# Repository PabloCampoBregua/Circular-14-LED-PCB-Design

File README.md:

# Circular LED PCB

Design and development of a four-layer circular PCB featuring a 14-LED array for illumination purposes, designed using **KiCad 9.0**.

## Project Overview

This project focuses on the design of a compact circular printed circuit board (PCB) with 14 LEDs arranged in two concentric rings.

The PCB uses a four-layer architecture to simplify power distribution and ground connections while keeping the individual LED circuits properly routed.

## Technical Specifications

- **EDA software:** KiCad 9.0
- **PCB type:** Four-layer PCB
- **LED configuration:** 14 LEDs arranged in two concentric rings
- **LED drivers:** Individual series resistor for each LED
- **Power distribution:** Dedicated internal copper layer
- **Ground distribution:** Dedicated internal copper layer

## PCB Layer Stack-up

| Layer | Function |
|---|---|
| F.Cu | LED components and signal routing |
| In1.Cu | Ground plane (GND) |
| In2.Cu | Power distribution plane (+V) |
| B.Cu | Current-limiting resistors and routing |

## Design Features

- Circular PCB geometry.
- Two concentric LED arrays.
- Individual current-limiting resistors for each LED.
- Dedicated internal copper planes for power and ground distribution.
- Through-hole vias connecting surface components to internal copper layers.

## Repository Structure

- `.kicad_pro` – KiCad project configuration.
- `.kicad_pcb` – PCB layout.
- `.kicad_sch` – Electrical schematic, if available.
- `README.md` – Project documentation.

## PCB Design

### 3D View

### Front View

### Back View

## Tools

- KiCad 9.0

## Project Status

PCB layout and routing completed. Final design validation pending.

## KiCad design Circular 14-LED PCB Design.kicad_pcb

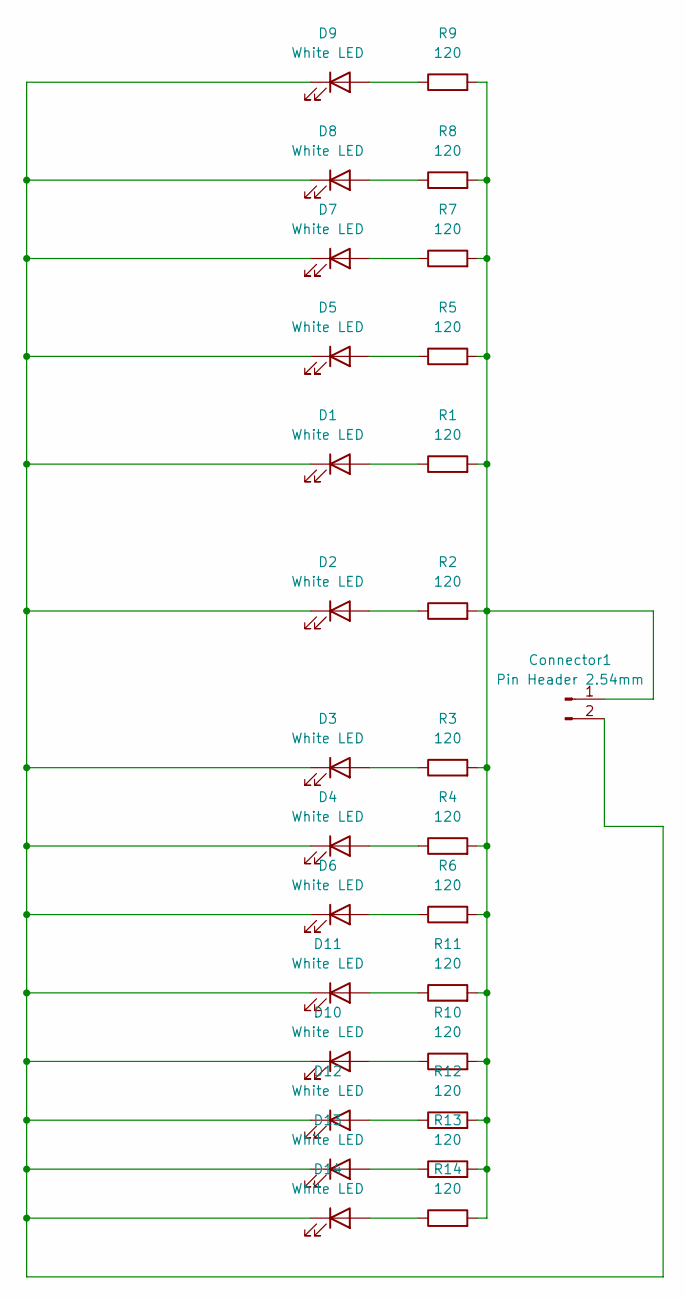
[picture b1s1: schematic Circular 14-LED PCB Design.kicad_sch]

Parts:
Connector1: Pin Header 2.54mm; PinHeader_1x02_P2.54mm_Vertical
D1, D2, D3, D4, D5, D6, D7, D8, D9, D10, D11, D12, D13, D14: White LED; LED_1206_3216Metric_Pad1.42x1.75mm_HandSolder
R1, R2, R3, R4, R5, R6, R7, R8, R9, R10, R11, R12, R13, R14: 120; R_1206_3216Metric_Pad1.30x1.75mm_HandSolder

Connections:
unnamed: Connector1.1, R1.2, R2.2, R3.2, R4.2, R5.2, R6.2, R7.2, R8.2, R9.2, R10.2, R11.2, R12.2, R13.2, R14.2
unnamed: Connector1.2, D1.1 (K), D2.1 (K), D3.1 (K), D4.1 (K), D5.1 (K), D6.1 (K), D7.1 (K), D8.1 (K), D9.1 (K), D10.1 (K), D11.1 (K), D12.1 (K), D13.1 (K), D14.1 (K)
unnamed: D1.2 (A), R1.1
unnamed: D2.2 (A), R2.1
unnamed: D3.2 (A), R3.1
unnamed: D4.2 (A), R4.1
unnamed: D5.2 (A), R5.1
unnamed: D6.2 (A), R6.1
unnamed: D7.2 (A), R7.1
unnamed: D8.2 (A), R8.1
unnamed: D9.2 (A), R9.1
unnamed: D10.2 (A), R10.1
unnamed: D11.2 (A), R11.1
unnamed: D12.2 (A), R12.1
unnamed: D13.2 (A), R13.1
unnamed: D14.2 (A), R14.1

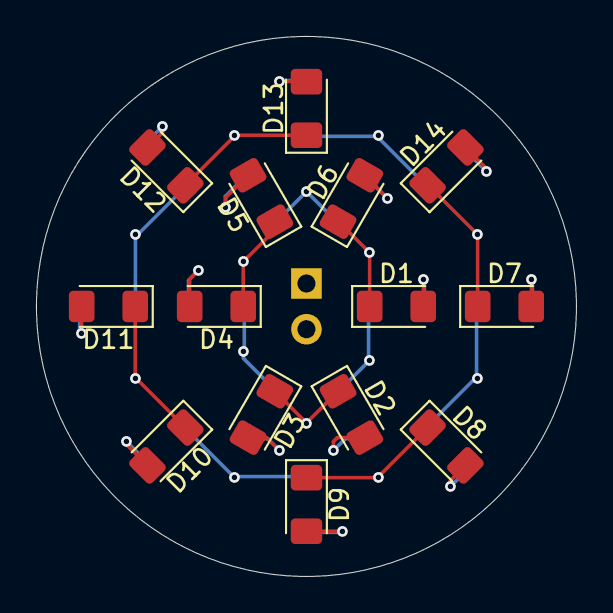
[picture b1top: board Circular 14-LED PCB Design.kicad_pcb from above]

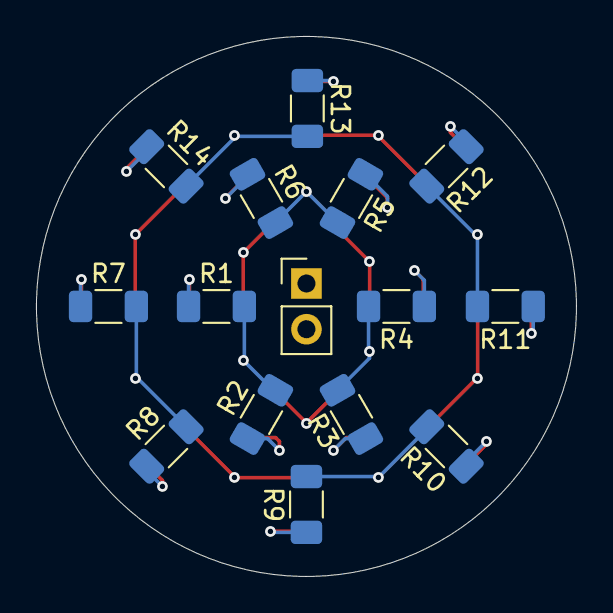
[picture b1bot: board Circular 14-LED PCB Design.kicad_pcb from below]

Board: 4 copper layers, 30.0 x 30.0 mm, 29 parts (15 on the bottom side), 16 nets.
